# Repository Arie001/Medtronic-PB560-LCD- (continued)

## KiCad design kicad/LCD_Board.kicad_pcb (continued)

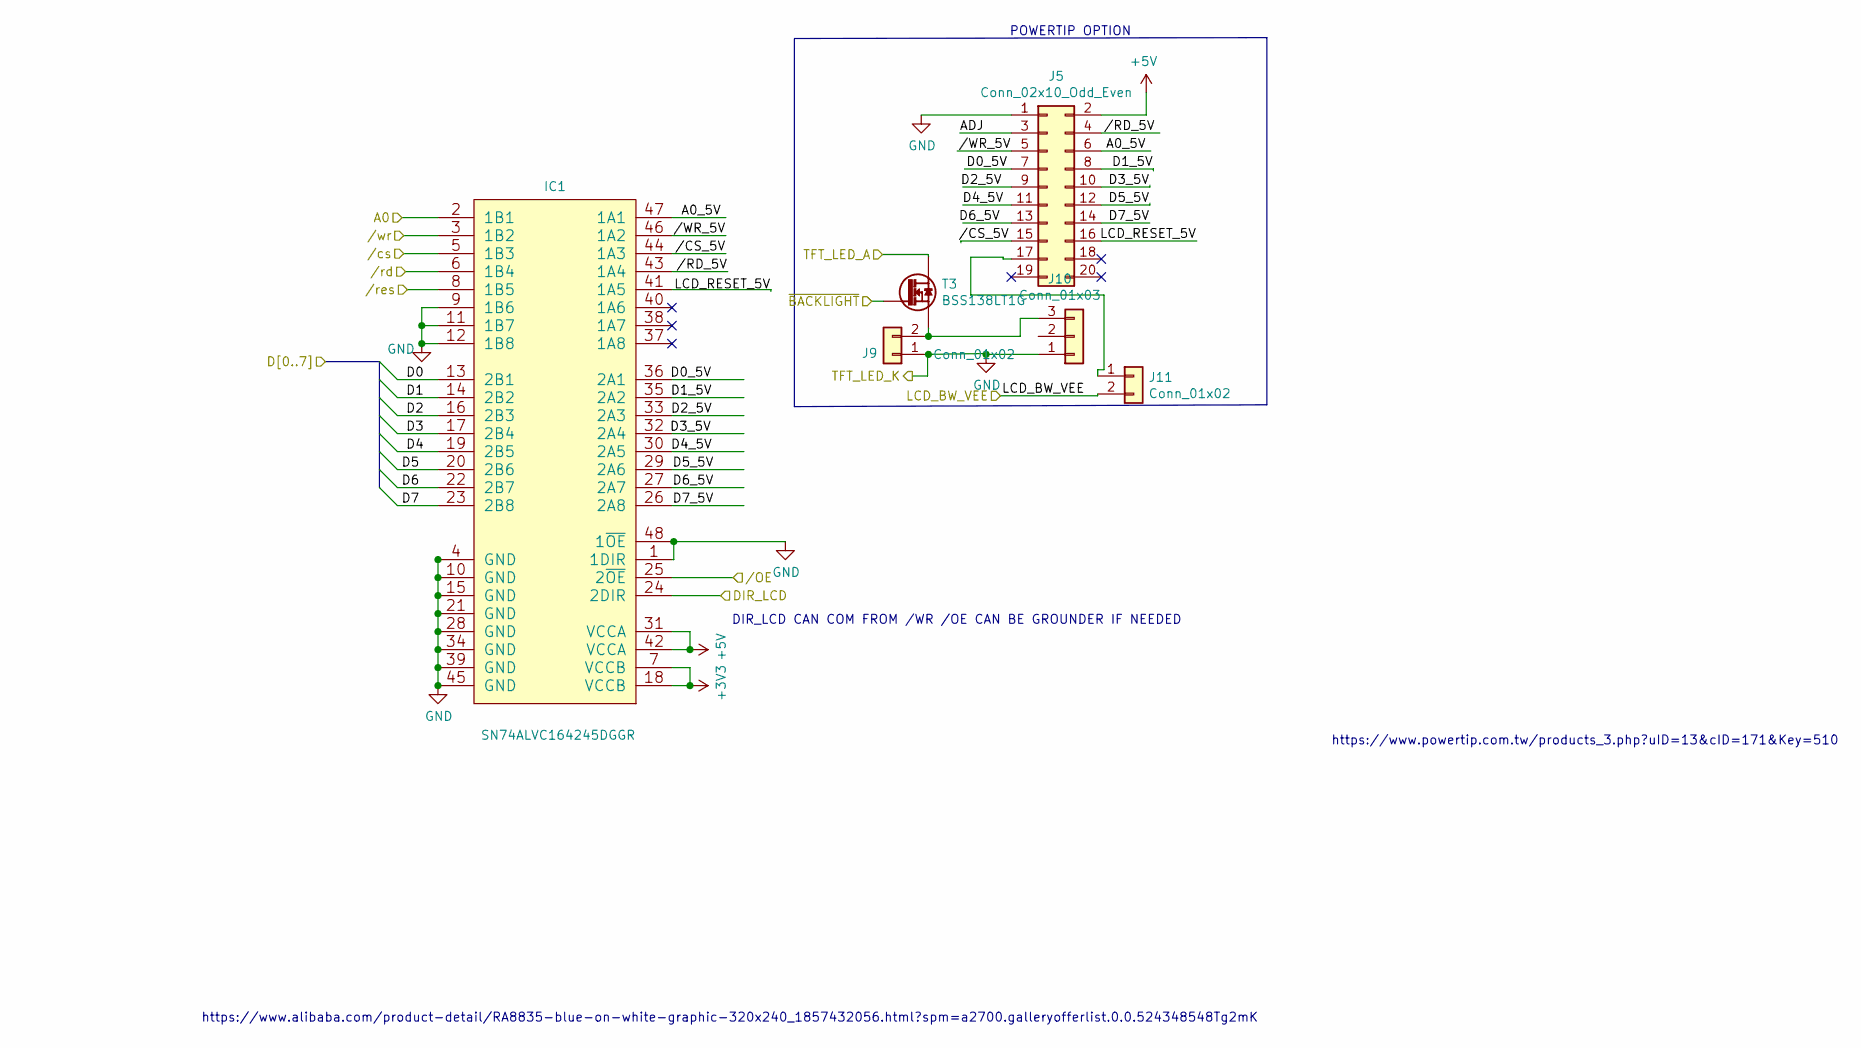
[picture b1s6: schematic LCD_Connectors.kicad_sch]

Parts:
IC1: SN74ALVC164245DGGR; TSSOP-48_6.1x12.5mm_P0.5mm; Part Number SN74ALVC164245DGGR; lcsc C7128
J5: Conn_02x10_Odd_Even; PinHeader_2x10_P2.54mm_Horizontal
J9: Conn_01x02; PinHeader_1x02_P2.54mm_Horizontal
J10: Conn_01x03; JST_SM03(4.0)B-BHS-1-TB
J11: Conn_01x02; PinHeader_1x02_P2.54mm_Vertical
T3: BSS138LT1G; SOT-23_Handsoldering; Part Number BSS138LT1G; lcsc C8490

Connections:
+3V3: IC1.7 (VCCB), IC1.18 (VCCB); also elsewhere on the board
+5V: IC1.31 (VCCA), IC1.42 (VCCA), J5.2; also elsewhere on the board
/A0_mico: IC1.2 (1B1); also elsewhere on the board
/D0: IC1.13 (2B1); also elsewhere on the board
/D1: IC1.14 (2B2); also elsewhere on the board
/D2: IC1.16 (2B3); also elsewhere on the board
/D3: IC1.17 (2B4); also elsewhere on the board
/D4: IC1.19 (2B5); also elsewhere on the board
/D5: IC1.20 (2B6); also elsewhere on the board
/D6: IC1.22 (2B7); also elsewhere on the board
/D7: IC1.23 (2B8); also elsewhere on the board
/DIR_LCD: IC1.24 (2DIR); also elsewhere on the board
/LCD_BW_VEE: J11.2; also elsewhere on the board
/LCD_Connectors/A0_5V: IC1.47 (1A1), J5.6
/LCD_Connectors/D0_5V: IC1.36 (2A1), J5.7
/LCD_Connectors/D1_5V: IC1.35 (2A2), J5.8
/LCD_Connectors/D2_5V: IC1.33 (2A3), J5.9
/LCD_Connectors/D4_5V: IC1.30 (2A5), J5.11
/LCD_Connectors/D5_5V: IC1.29 (2A6), J5.12
/LCD_Connectors/D6_5V: IC1.27 (2A7), J5.13
/LCD_Connectors/D7_5V: IC1.26 (2A8), J5.14
/LCD_Connectors/LCD_RESET_5V: IC1.41 (1A5), J5.16
/LCD_Connectors//CS_5V: IC1.44 (1A3), J5.15
/LCD_Connectors//RD_5V: IC1.43 (1A4), J5.4
/LCD_Connectors//WR_5V: IC1.46 (1A2), J5.5
/Micro_CS: IC1.5 (1B3); also elsewhere on the board
/TFT_LED_A: T3.3 (D); also elsewhere on the board
//LCD_RST: IC1.8 (1B5); also elsewhere on the board
//Micro_wr: IC1.3 (1B2); also elsewhere on the board
//OE: IC1.25 (2~OE); also elsewhere on the board
//mico_RD: IC1.6 (1B4); also elsewhere on the board
/~BACKLIGHT~: T3.1 (G); also elsewhere on the board
GND: IC1.1 (1DIR), IC1.4 (GND), IC1.9 (1B6), IC1.10 (GND), IC1.11 (1B7), IC1.12 (1B8), IC1.15 (GND), IC1.21 (GND), IC1.28 (GND), IC1.34 (GND), IC1.39 (GND), IC1.45 (GND), IC1.48 (1~OE), J5.1, J9.1, J10.1; also elsewhere on the board
unnamed: J9.2, J10.3, T3.2 (S)
unnamed: J5.17, J11.1

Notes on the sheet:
POWERTIP OPTION
DIR_LCD CAN COM FROM /WR /OE CAN BE GROUNDER IF NEEDED
https://www.alibaba.com/product-detail/RA8835-blue-on-white-graphic-320x240_1857432056.html?spm=a2700.galleryofferlist.0.0.524348548Tg2mK
https://www.powertip.com.tw/products_3.php?uID=13&cID=171&Key=510

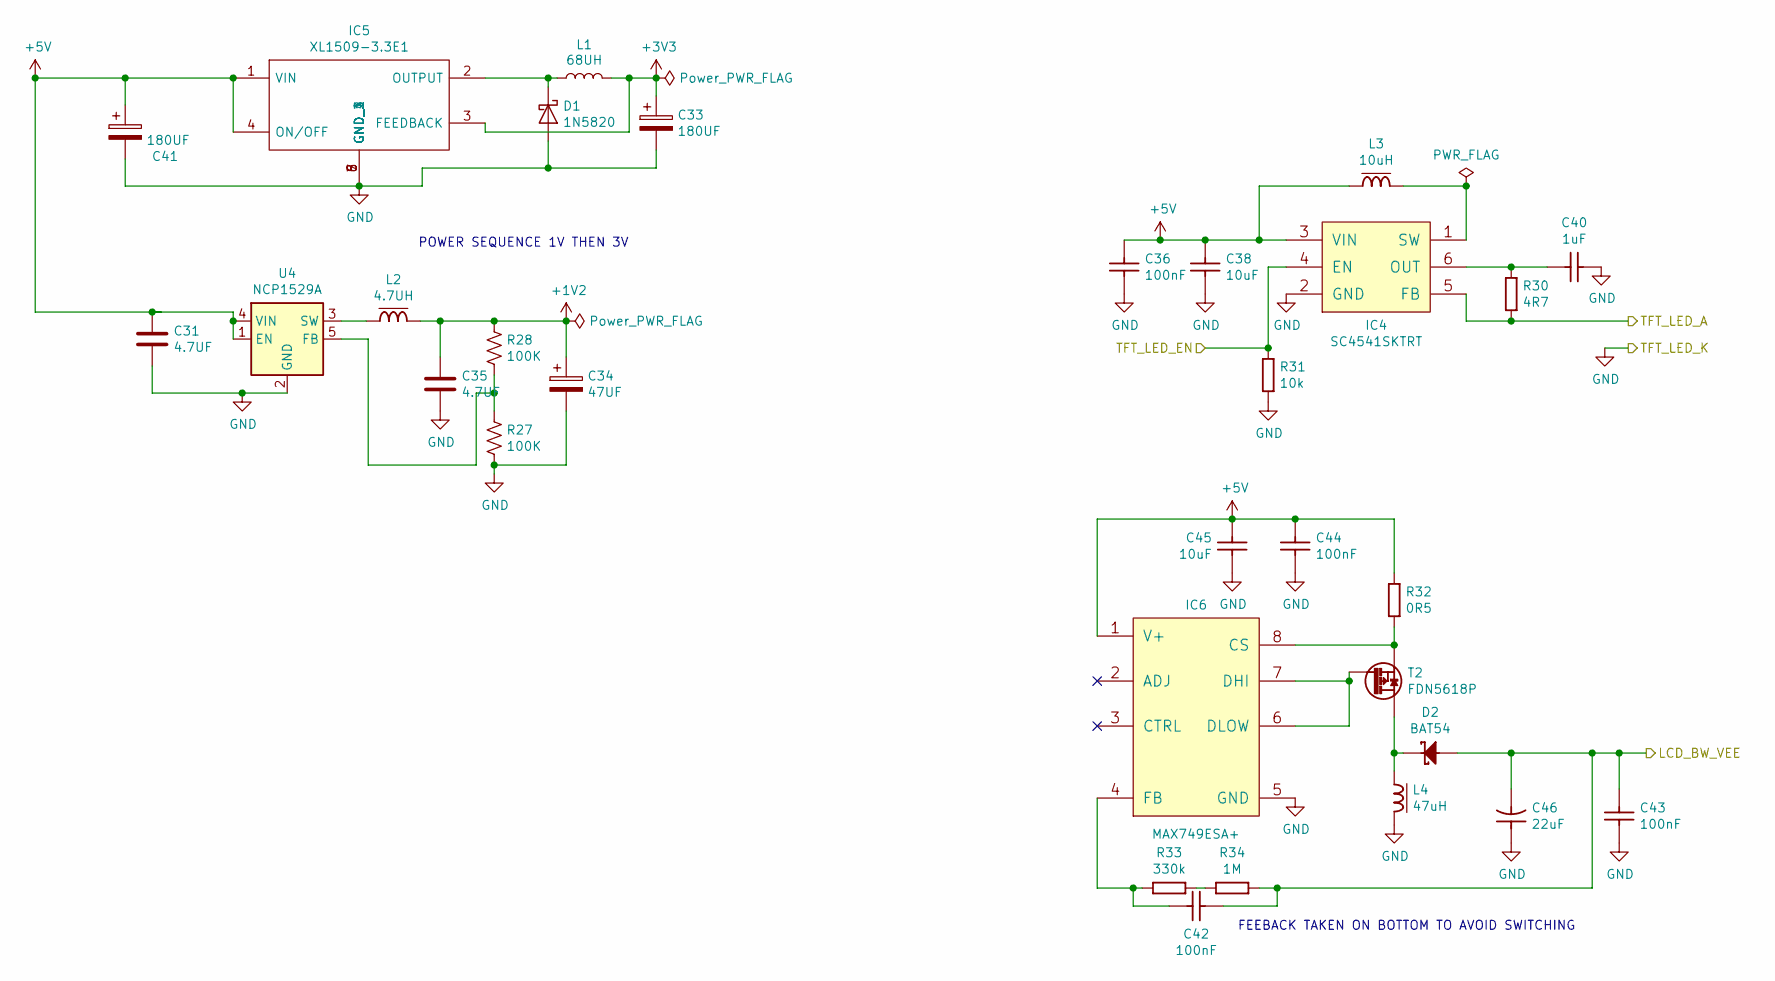
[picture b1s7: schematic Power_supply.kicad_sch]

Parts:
C31, C35: 4.7UF; C_0603_1608Metric_Pad0.99x1.00mm_HandSolder
C33, C41: 180UF; CP_Elec_6.3x5.9
C34: 47UF; CAPMP7343X310N
C36, C42, C43, C44: CC0603_100NF_50V_10%_X7R; C_0603_1608Metric_Pad0.99x1.00mm_HandSolder; Voltage 50V; Tolerance ±10%; Part Number CC0603_100NF_50V_10%_X7R
C38: CC0603_10UF_16V_20%_X5R; C_1206_3216Metric; Voltage 16V; Tolerance ±20%; Part Number CC0603_10UF_16V_20%_X5R
C40: CC0805_1UF_35V_20%_X7R; C_0603_1608Metric_Pad0.99x1.00mm_HandSolder; Voltage 35V; Tolerance ±20%; Part Number CC0805_1UF_35V_20%_X7R
C45: 1206_10UF_16V_20%_X5R; C_1206_3216Metric_Pad1.39x1.80mm_HandSolder; Voltage 16V; Tolerance ±20%; Part Number CC0603_10UF_16V_20%_X5R
C46: CTE7343-31_22UF_35V_10%; CP_EIA-3528-21_Kemet-B; Voltage 35V; Tolerance ±10%; Part Number CTE7343-31_22UF_35V_10%
D1: 1N5820; D_SMC
D2: BAT54; SOT95P240X130-3N; Voltage 30V; Part Number BAT54
IC4: SC4541SKTRT; SOT95P280X100-6N; Part Number SC4541SKTRT; lcsc digi SC4541SKTR-ND
IC5: XL1509-3.3E1; SOIC-8_3.9x4.9mm_P1.27mm; Manufacturer_Part_Number XL1509-5.0E1; lcsc C74193
IC6: MAX749ESA+; SOIC-8_3.9x4.9mm_P1.27mm; Part Number MAX749ESA+; lcsc digo MAX749ESA+-ND
L1: 68UH; IND_MURATA-PS_8400
L2: IND_10UH_10%_MURATA-PS_8400-Inductors_SMD; IND_MURATA-PS_8400; Tolerance ±10%; Part Number IND_10UH_10%_MURATA-PS_8400
L3: IND_10UH_10%_MURATA-PS_8400; IND_MURATA-PS_8400; Tolerance ±10%; Part Number IND_10UH_10%_MURATA-PS_8400
L4: IND_47UH_10%_MURATA-PS_8400; IND_MURATA-PS_8400; Tolerance ±10%; Part Number IND_47UH_10%_MURATA-PS_8400
R27, R28: 100K; R_0603_1608Metric_Pad0.99x1.00mm_HandSolder
R30: R1206_4R7_1%_0.25W_200PPM; R_0603_1608Metric_Pad0.99x1.00mm_HandSolder; Tolerance ±1%; Part Number R1206_4R7_1%_0.25W_200PPM
R31: R0402_10K_1%_0.0625W_100PPM; R_0603_1608Metric_Pad0.99x1.00mm_HandSolder; Tolerance ±1%; Part Number R0402_10K_1%_0.0625W_100PPM
R32: R0805_0R5_1%_0.125W_200PPM; R_0603_1608Metric_Pad0.99x1.00mm_HandSolder; Tolerance ±1%; Part Number R0805_0R5_1%_0.125W_200PPM
R33: R0603_330K_1%_0.1W_100PPM; R_0603_1608Metric_Pad0.99x1.00mm_HandSolder; Tolerance ±1%; Part Number R0603_330K_1%_0.1W_100PPM
R34: R0402_1M_1%_0.0625W_100PPM; R_0603_1608Metric_Pad0.99x1.00mm_HandSolder; Tolerance ±1%; Part Number R0402_1M_1%_0.0625W_100PPM
T2: FDN5618P; SOT-23_Handsoldering; Part Number FDN5618P; lcsc C400792
U4: NCP1529A; SOT-23-5; lcsc C23902

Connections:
+1V2: C34.1, C35.1, L2.2, R28.1; also elsewhere on the board
+3V3: C33.1, IC5.3 (FEEDBACK), L1.2; also elsewhere on the board
+5V: C31.1, C36.1, C38.1, C41.1, C44.1, C45.1, IC4.3 (VIN), IC5.1 (VIN), IC5.4 (ON/OFF), IC6.1 (V+), L3.1, R32.1, U4.1 (EN), U4.4 (VIN); also elsewhere on the board
/LCD_BW_VEE: C42.2, C43.1, C46.2, D2.1 (A), R34.2; also elsewhere on the board
/Power_supply/TFT_LED_EN: IC4.4 (EN), R31.1
/TFT_LED_A: IC4.5 (FB), R30.1; also elsewhere on the board
GND: C31.2, C33.2, C34.2, C35.2, C36.2, C38.2, C40.2, C41.2, C43.2, C44.2, C45.2, C46.1, D1.2 (A), IC4.2 (GND), IC5.5 (GND_1), IC5.6 (GND_2), IC5.7 (GND_3), IC5.8 (GND_4), IC6.5 (GND), L4.2, R27.2, R31.2, U4.2 (GND); also elsewhere on the board
unnamed: C40.1, IC4.6 (OUT), R30.2
unnamed: C42.1, IC6.4 (FB), R33.1
unnamed: D1.1 (K), IC5.2 (OUTPUT), L1.1
unnamed: D2.3 (C), L4.1, T2.3 (D)
unnamed: IC4.1 (SW), L3.2
unnamed: IC6.6 (DLOW), IC6.7 (DHI), T2.1 (G)
unnamed: IC6.8 (CS), R32.2, T2.2 (S)
unnamed: L2.1, U4.3 (SW)
unnamed: R27.1, R28.2, U4.5 (FB)
unnamed: R33.2, R34.1

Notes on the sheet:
POWER SEQUENCE 1V THEN 3V
FEEBACK TAKEN ON BOTTOM TO AVOID SWITCHING

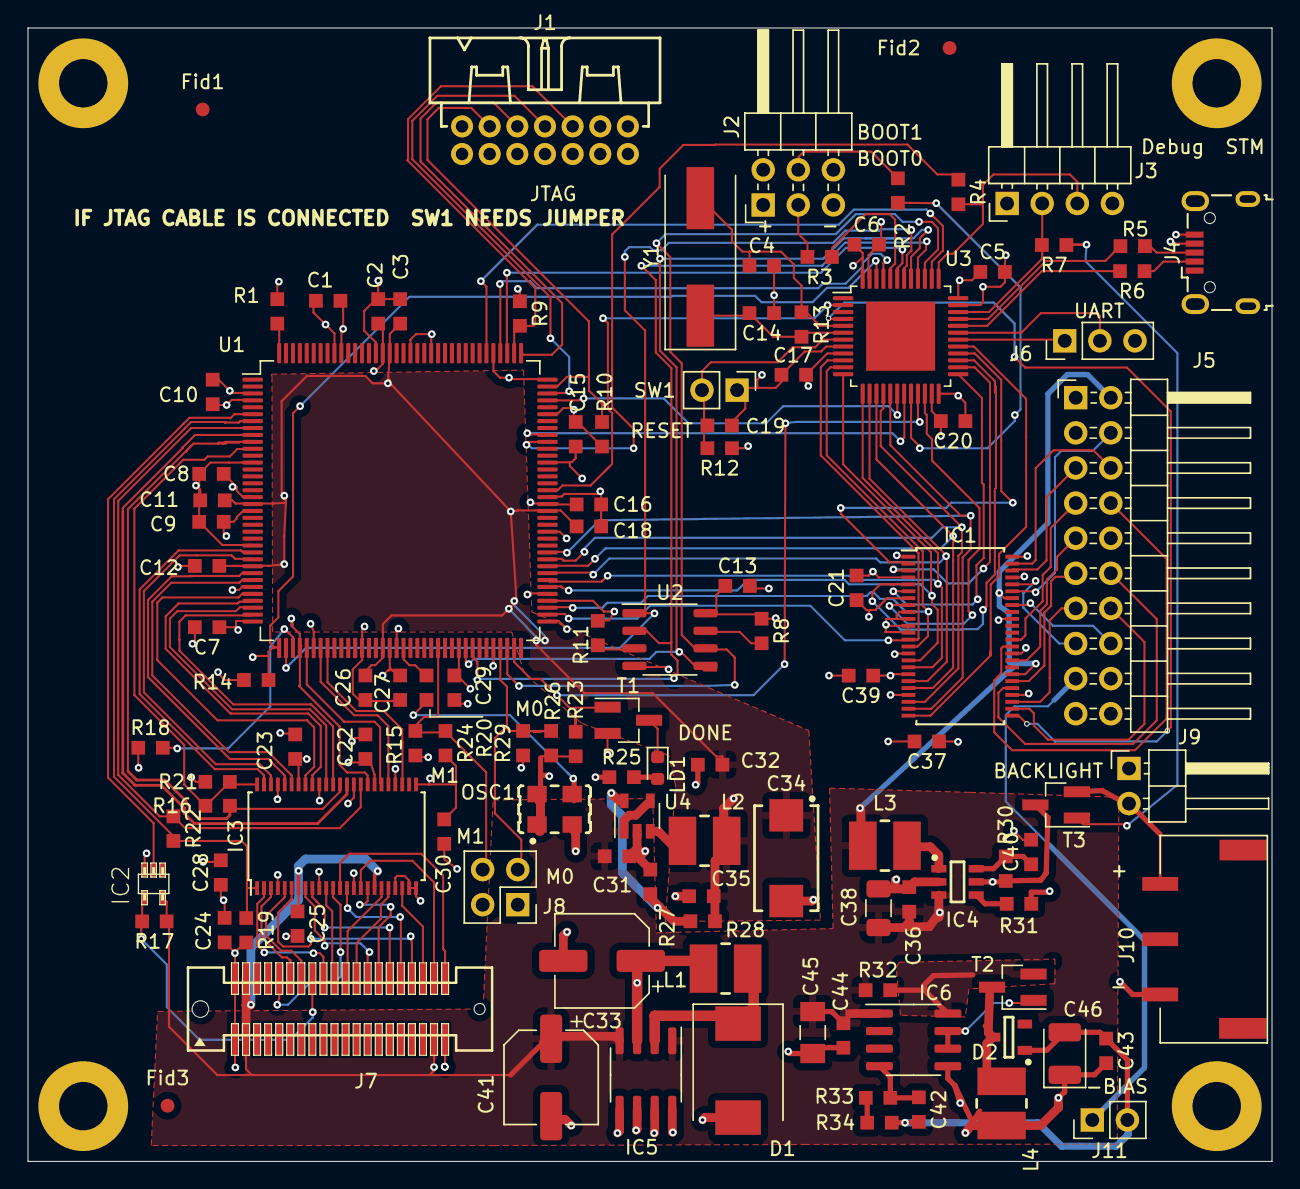
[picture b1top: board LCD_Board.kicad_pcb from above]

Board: 4 copper layers, 90.0 x 82.0 mm, 121 parts (0 on the bottom side), 123 nets.

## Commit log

2020-09-23 Upload
    First Share on Github The VHDL has changed a bit but the STM32 is the Major Issue. The Software Needs to recreate all the HMI Display Funtions .
    That Is Far Beyond what I am able to Contribute
2020-09-24 update
    update files
